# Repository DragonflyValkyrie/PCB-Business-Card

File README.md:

# PCB Business Card

## Schematics

## PCB Desgin

## Features:
- NFC functions: Tap your phone on the card to my GitHub.
- GitHub QR Code: Don't want to tap? Scan it! Dive into my GitHub.
- Power Wheel Formula: Quick power calculations. Because who doesn't need a handy formula?
- Ruler: Inches or centimeters, not just a paperweight or a game card. Inspired by Anthony Kouttron’s genius
- Snake Game: Play Snake on LEDs, a nod to Ryan Chen's Tic-Tac-Toe masterpiece. Classic gaming meets the business card – why not?
- Power Source: Powered by a sneaky CR2032 coin battery, borrowed from Brian McEvoy's idea.

## Inspirations:
- Anthony Kouttron's Ruler and Design: (Read more [here](https://hackaday.com/2019/11/19/theres-more-to-designing-a-pcb-business-card-than-meets-the-eye/)) - Because sometimes you just need to measure things on the fly.
- Ryan Chen's Tic-Tac-Toe Challenge: (Explore more [here](https://hackaday.com/tag/business-card/)) - I turned tic-tac-toe into Snake – A different approach to pass the time.
- Brian McEvoy's Literally Flashy Business Cards: (See the blink [here](https://hackaday.com/2017/10/04/literally-flashy-business-cards/)) - When your business card needs to leave an impression and be thin.

## Design Choices

### NFC Design

### QR Code

### Components

### Snake Game

## Bill of Materials (BOM)

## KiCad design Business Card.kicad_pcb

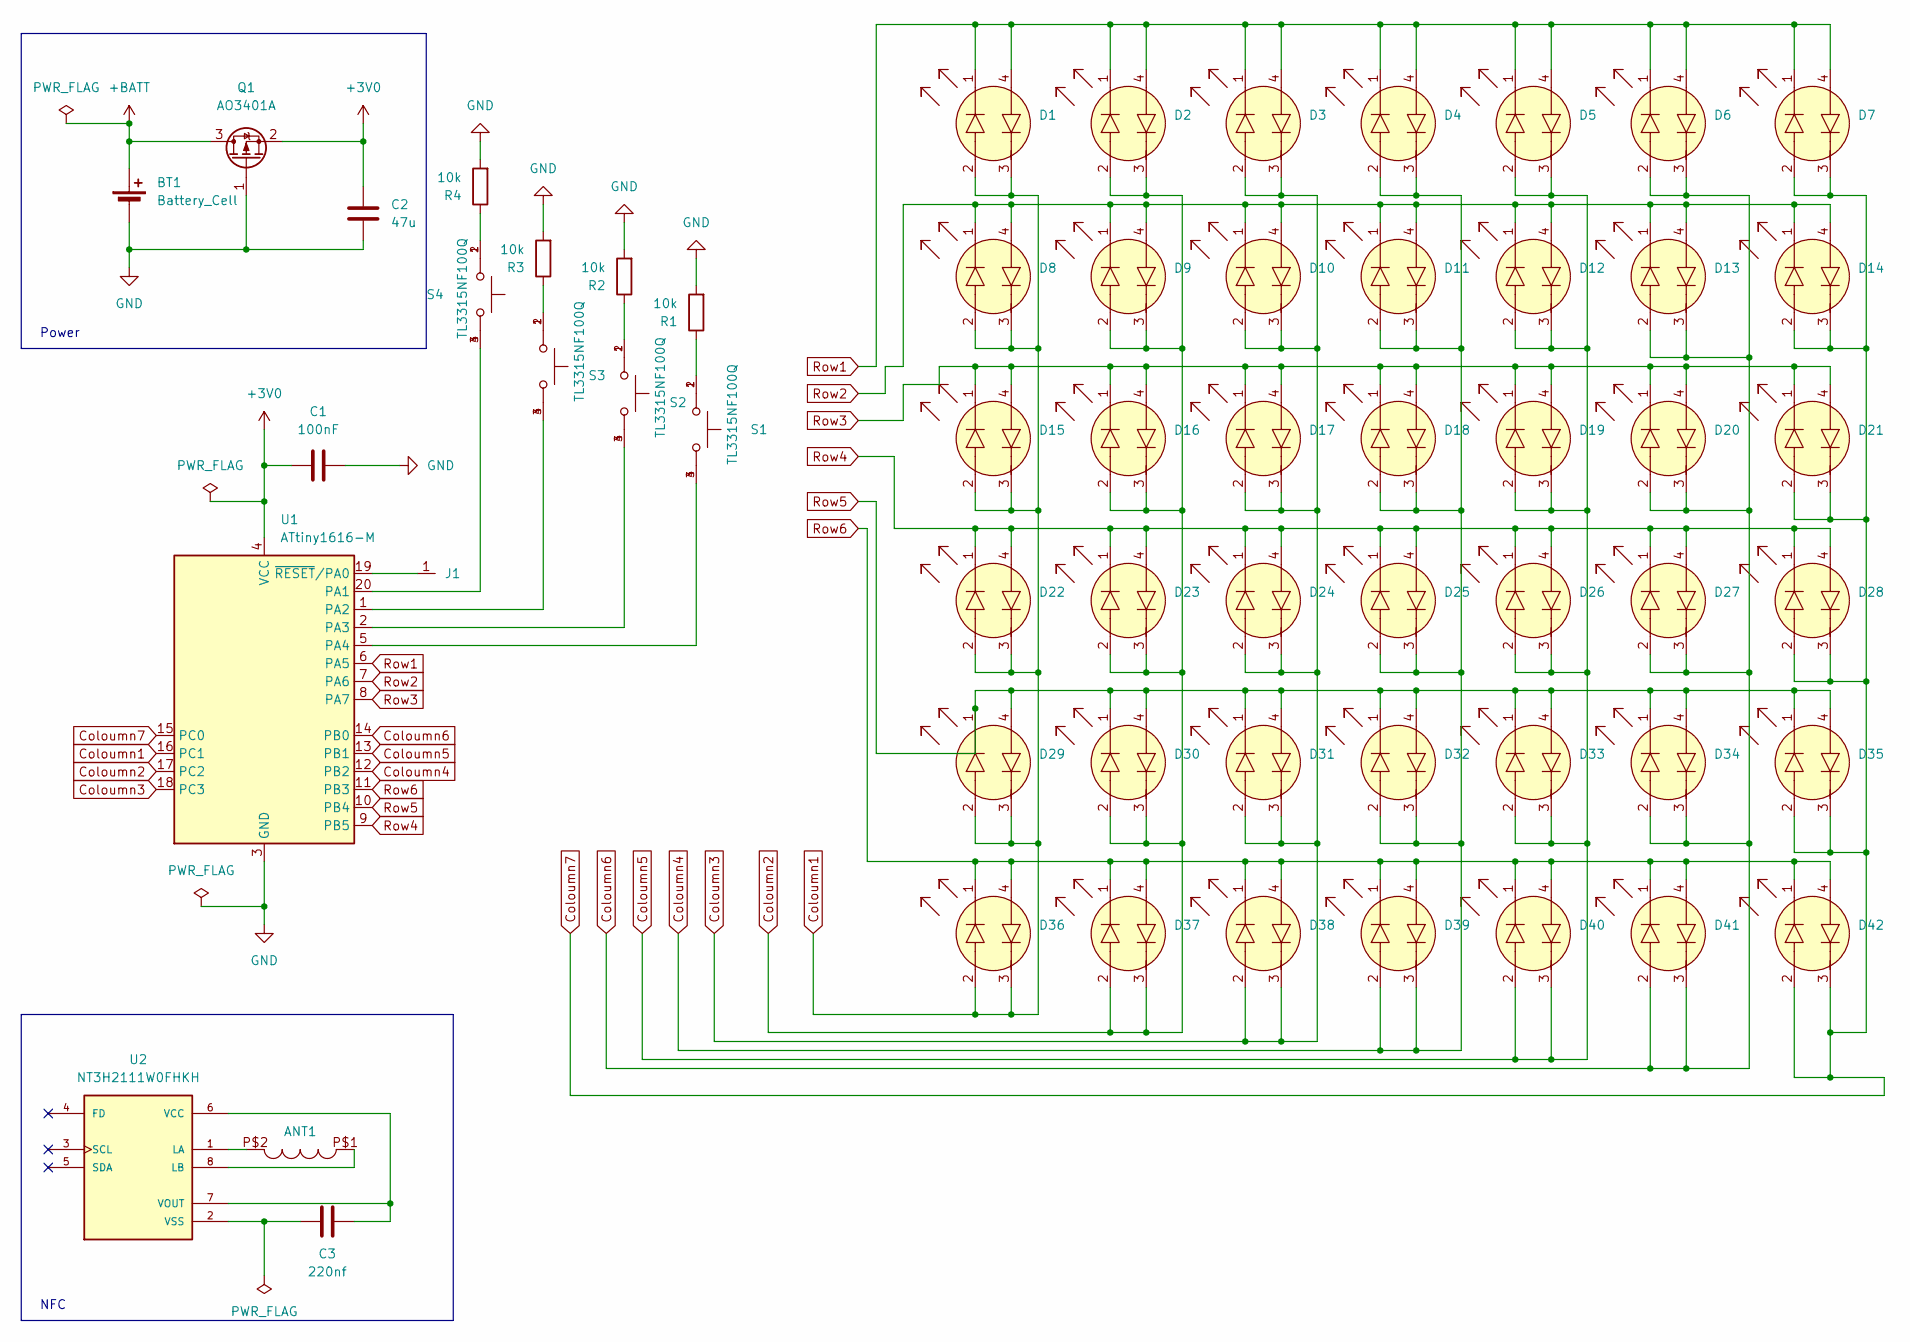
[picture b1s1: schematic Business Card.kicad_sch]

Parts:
ANT1: 25X48MM_NFC_ANTENNA
BT1: Battery_Cell; Coin_Cell
C1: 100nF; C_0603_1608Metric
C2: 47u; C_0603_1608Metric
C3: 220nf; C_0603_1608Metric
D1, D2, D3, D4, D5, D6, D7, D8, D9, D10, D11, D12, D13, D14, D15, D16, D17, D18, D19, D20, D21, D22, D23, D24, D25, D26, D27, D28, D29, D30, D31, D32, D33, D34, D35, D36, D37, D38, D39, D40, D41, D42: XL-1615SURSYGC_LED
J1: Progam_Pad
Q1: AO3401A; SOT-23; LCSC C15127
R1, R2, R3, R4: 10k; R_0603_1608Metric
S1, S2, S3, S4: TL3315NF100Q; SW_TL3315NF100Q
U1: ATtiny1616-M; VQFN-20-1EP_3x3mm_P0.4mm_EP1.7x1.7mm
U2: NT3H2111W0FHKH; QFN8P50_160X160X50L40X20N

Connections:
+3V0: C1.2, C2.1, Q1.2 (S), U1.4 (VCC)
+BATT: BT1.1 (+), Q1.3 (D)
Coloumn1: D1.2, D1.3, D8.2, D8.3, D15.2, D15.3, D22.2, D22.3, D29.2, D29.3, D36.2, D36.3, U1.16 (PC1)
Coloumn2: D2.2, D2.3, D9.2, D9.3, D16.2, D16.3, D23.2, D23.3, D30.2, D30.3, D37.2, D37.3, U1.17 (PC2)
Coloumn3: D3.2, D3.3, D10.2, D10.3, D17.2, D17.3, D24.2, D24.3, D31.2, D31.3, D38.2, D38.3, U1.18 (PC3)
Coloumn4: D4.2, D4.3, D11.2, D11.3, D18.2, D18.3, D25.2, D25.3, D32.2, D32.3, D39.2, D39.3, U1.12 (PB2)
Coloumn5: D5.2, D5.3, D12.2, D12.3, D19.2, D19.3, D26.2, D26.3, D33.2, D33.3, D40.2, D40.3, U1.13 (PB1)
Coloumn6: D6.2, D6.3, D13.2, D13.3, D20.2, D20.3, D27.2, D27.3, D34.2, D34.3, D41.2, D41.3, U1.14 (PB0)
Coloumn7: D7.2, D7.3, D14.2, D14.3, D21.2, D21.3, D28.2, D28.3, D35.2, D35.3, D42.2, D42.3, U1.15 (PC0)
GND: BT1.2 (-), C1.1, C2.2, Q1.1 (G), R1.2, R2.2, R3.2, R4.2, U1.3 (GND), U1.21 (GND)
unnamed: R1.1, S1.1, S1.2
unnamed: R2.1, S2.1, S2.2
unnamed: R3.1, S3.1, S3.2
unnamed: R4.1, S4.1, S4.2
unnamed: S4.3, S4.4, U1.20 (PA1)
unnamed: S3.3, S3.4, U1.1 (PA2)
unnamed: S2.3, S2.4, U1.2 (PA3)
unnamed: S1.3, S1.4, U1.5 (PA4)
unnamed: J1.1, U1.19 (~RESET/PA0)
unnamed: ANT1.P$2, U2.1 (LA)
unnamed: ANT1.P$1, U2.8 (LB)
unnamed: C3.1, U2.6 (VCC), U2.7 (VOUT)
unnamed: C3.2, U2.2 (VSS)
Row1: D1.1, D1.4, D2.1, D2.4, D3.1, D3.4, D4.1, D4.4, D5.1, D5.4, D6.1, D6.4, D7.1, D7.4, U1.6 (PA5)
Row2: D8.1, D8.4, D9.1, D9.4, D10.1, D10.4, D11.1, D11.4, D12.1, D12.4, D13.1, D13.4, D14.1, D14.4, U1.7 (PA6)
Row3: D15.1, D15.4, D16.1, D16.4, D17.1, D17.4, D18.1, D18.4, D19.1, D19.4, D20.1, D20.4, D21.1, D21.4, U1.8 (PA7)
Row4: D22.1, D22.4, D23.1, D23.4, D24.1, D24.4, D25.1, D25.4, D26.1, D26.4, D27.1, D27.4, D28.1, D28.4, U1.9 (PB5)
Row5: D29.1, D29.4, D30.1, D30.4, D31.1, D31.4, D32.1, D32.4, D33.1, D33.4, D34.1, D34.4, D35.1, D35.4, U1.10 (PB4)
Row6: D36.1, D36.4, D37.1, D37.4, D38.1, D38.4, D39.1, D39.4, D40.1, D40.4, D41.1, D41.4, D42.1, D42.4, U1.11 (PB3)

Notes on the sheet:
Power
NFC

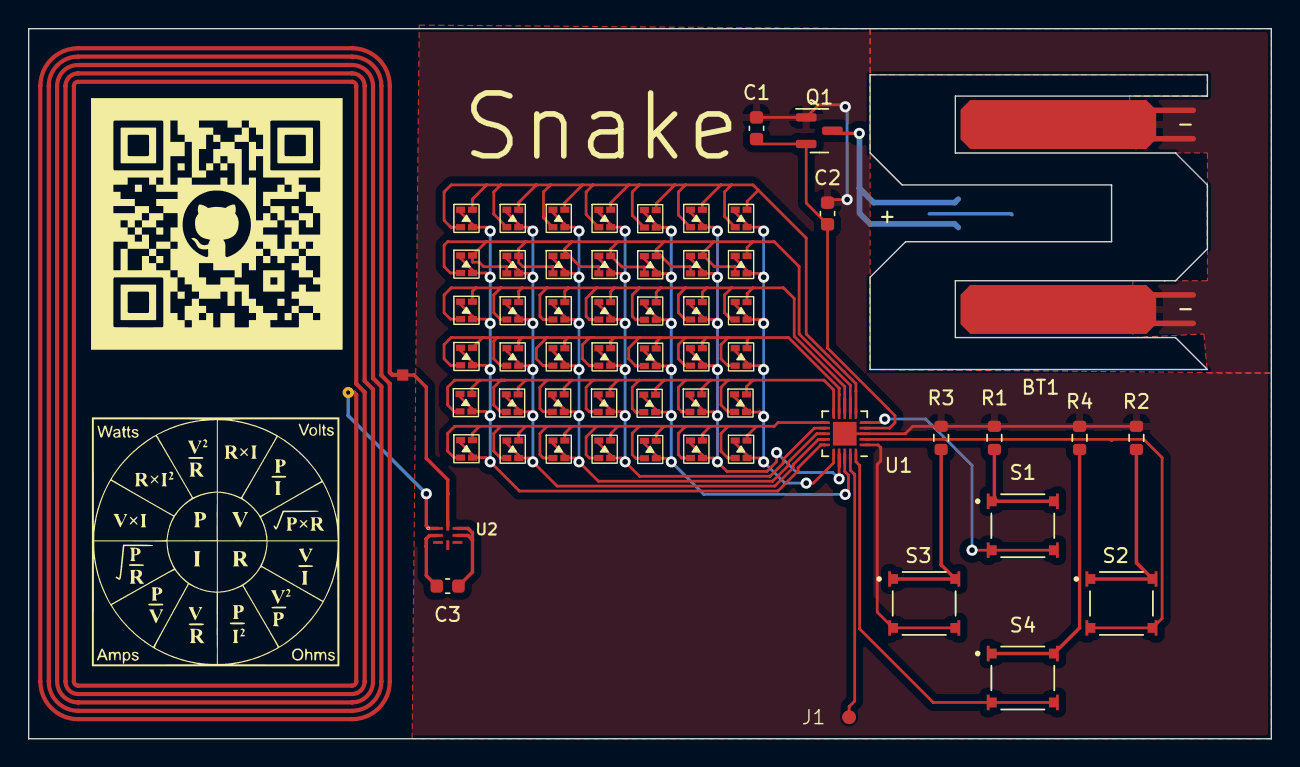
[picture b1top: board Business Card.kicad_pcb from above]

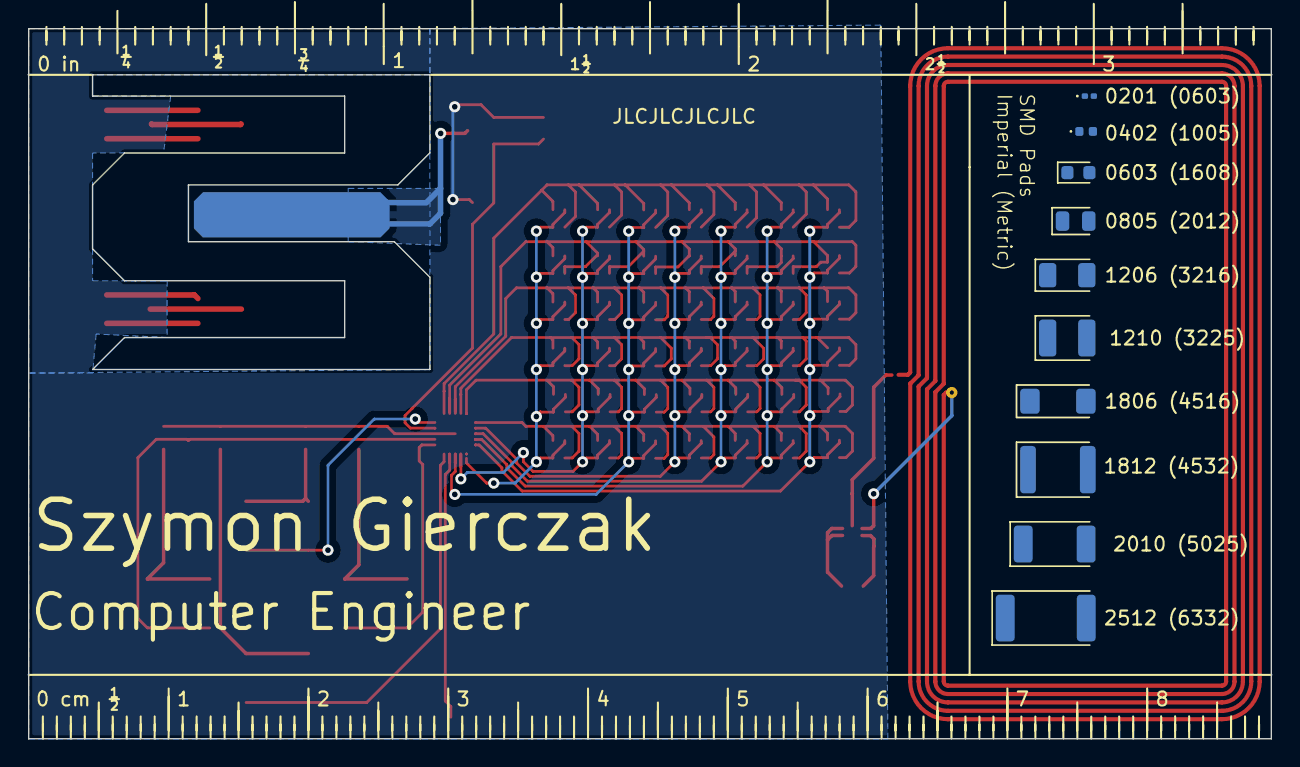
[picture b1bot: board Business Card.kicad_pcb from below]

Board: 2 copper layers, 88.9 x 50.8 mm, 69 parts (10 on the bottom side), 29 nets.

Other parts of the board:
0201 (0603): LED_0201_0603Metric
0402 (1005): LED_0402_1005Metric
0603 (1608): LED_0603_1608Metric
0805 (2012): LED_0805_2012Metric
1206 (3216): LED_1206_3216Metric
1210 (3225): LED_1210_3225Metric
1806 (4516): LED_1806_4516Metric
1812 (4532): LED_1812_4532Metric
2010 (5025): LED_2010_5025Metric
2512 (6332): LED_2512_6332Metric

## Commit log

2024-02-29 Updated Schematics and PCB
    Version 1 of schematics and PCB designed
2024-03-14 Board Edited
